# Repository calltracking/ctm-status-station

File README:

= CTM Status Station

The goal this project is to make it easy to have light in a room that helps people in the area know when someone is on a phone call.

We'll subscribe to incoming phone calls and active call events and change the light color to make this obvious

= Setup

Before the device is configured it will expose an access point: 
  ssid: ctmlight
  pass: ctmstatus

After connecting navigate browser to

http://192.168.4.1/

From the web interface configure your networks ssid and password

Once the device joins your network it'll blink green

You'll have to find the device now on your network

http://your-device-ip/

From here you can click connect and you'll be taken to a page on https://app.calltrackingmetrics give access to the device and you should 
next be presented with some options to choose a specific team or your whole account.

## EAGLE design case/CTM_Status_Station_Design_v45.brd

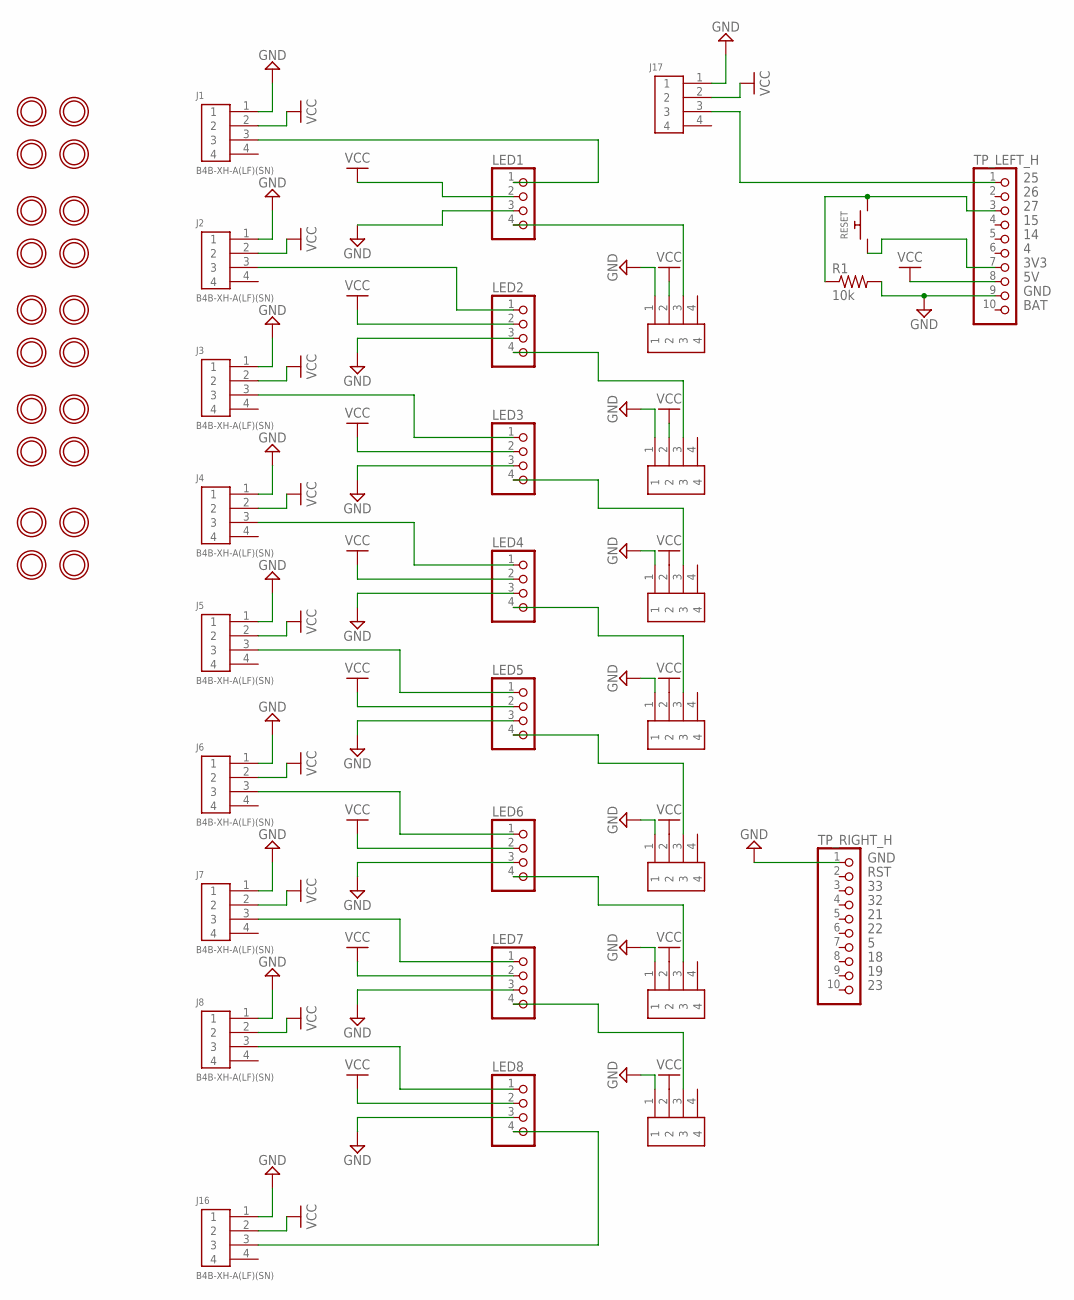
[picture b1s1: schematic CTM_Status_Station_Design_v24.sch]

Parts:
J1, J2, J3, J4, J5, J6, J7, J8, J9, J10, J11, J12, J13, J14, J15, J16, J17: B4B-XH-A(LF)(SN)
LED1, LED2, LED3, LED4, LED5, LED6, LED7, LED8: PINHD-1X4; 1X04
R1: 10k; 0207/7
RESET: SWITCH_PUSHBUTTONEVQ-PE; TACT_PANA-EVQ
TP_LEFT_H: PINHD-1X10; 1X10
TP_RIGHT_H: PINHD-1X10; 1X10
U$1, U$2, U$3, U$4, U$5, U$6, U$7, U$8, U$9, U$10, U$11, U$12, U$13, U$14, U$15, U$16, U$17, U$18, U$19, U$28: MOUNTINGHOLE2.5; MOUNTINGHOLE_2.5_PLATED

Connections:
3V3: RESET.P$1, TP_LEFT_H.7
DIN1: J1.3, LED1.1
DIN2: J2.3, LED2.1
DIN3: J3.3, LED3.1
DIN4: J4.3, LED4.1
DIN5: J5.3, LED5.1
DIN6: J6.3, LED6.1
DIN7: J7.3, LED7.1
DIN8: J8.3, LED8.1
DOUT: J17.3, TP_LEFT_H.1
DOUT1: J10.3, LED1.4
DOUT2: J9.3, LED2.4
DOUT3: J11.3, LED3.4
DOUT4: J12.3, LED4.4
DOUT5: J13.3, LED5.4
DOUT6: J14.3, LED6.4
DOUT7: J15.3, LED7.4
DOUT8: J16.3, LED8.4
GND: J1.1, J2.1, J3.1, J4.1, J5.1, J6.1, J7.1, J8.1, J9.1, J10.1, J11.1, J12.1, J13.1, J14.1, J15.1, J16.1, J17.1, LED1.3, LED2.3, LED3.3, LED4.3, LED5.3, LED6.3, LED7.3, LED8.3, R1.2, TP_LEFT_H.9, TP_RIGHT_H.1
RESET: R1.1, RESET.P$2, TP_LEFT_H.3
VCC: J1.2, J2.2, J3.2, J4.2, J5.2, J6.2, J7.2, J8.2, J9.2, J10.2, J11.2, J12.2, J13.2, J14.2, J15.2, J16.2, J17.2, LED1.2, LED2.2, LED3.2, LED4.2, LED5.2, LED6.2, LED7.2, LED8.2, TP_LEFT_H.8

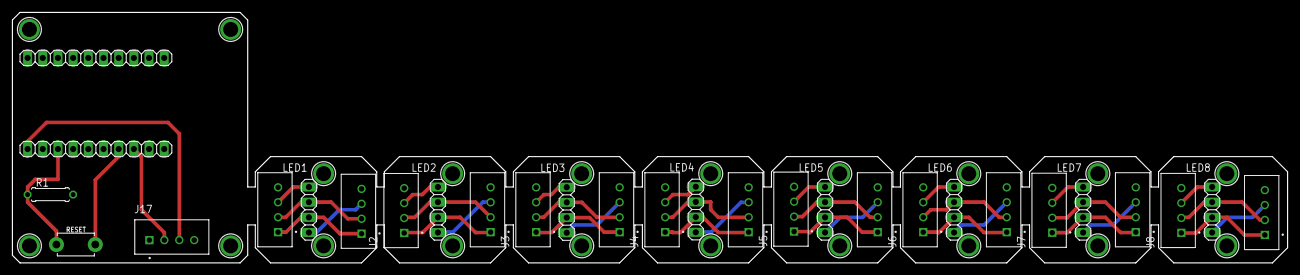
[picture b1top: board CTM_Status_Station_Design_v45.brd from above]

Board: 2 copper layers, 213.4 x 41.9 mm, 49 parts (0 on the bottom side), 21 nets.

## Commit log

2021-10-22 initial work
2021-10-22 formatting
2021-10-22 formating
2021-10-22 format
2021-10-25 more work on login flow
2021-10-30 work on adding a neopixel
2021-11-04 test socketio
2021-11-04 initial work based on active calls counter e.g. global status
2021-11-06 more work on settings
2021-11-07 finished testing with 4 leds... maybe we can try scaling this up 2 8?
2021-11-07 adding logic to handle socket re-connection (maybe don't need two booleans...)
2021-11-07 improve handling of refresh token to get a new access token
2021-11-09 fixing reset and fixed a crash caused by a serial printf
2021-11-11 tweaks and fetch status at boot
2021-11-12 change license
2021-11-12 working on some edge cases related bad memory data on the eeprom
2021-11-12 adding design files
2021-11-12 updating to print with higher temps
2021-11-13 refresh all on save
2021-11-13 update designs to optimize for faster print times and less material per case
2021-11-13 remove pcb peg's they are too small to print quickly
2021-11-13 slightly more optimized layout with 2 parts per print
2021-11-13 fix for ringers we have LED_COUNT ringers
2021-11-14 adding custom status light user defined colors
2021-11-14 sync status using group status call, limited to 10 agents per request but perfect for status station with only 8 led's per node
2021-11-21 refresh all statuses every 60 seconds polling
2021-11-21 make custom statues not as bright
2021-12-02 add 3mf files
2021-12-03 dimmer status lights
2021-12-04 ran into a long running case where the token expired
2021-12-16 usability updates, locate led and possible wifi recovery if lost
    - locate led will change led to yellow/orange for 10 seconds and then refetch status on all leds
    - wifi recovery if the wifi in the office is reset (common as we're getting the new office setup working)
    - we have 8 seats per cube run, this change does reset the device because of eeprom being invalid
2021-12-16 adding some design's for wiring and mounting to exterior cube walls
2021-12-17 fix issues related to led locate
2021-12-23 minor tweaks and notes on development
2022-03-02 update to EIO=4 from 3
2022-03-02 support encoding for lookup of agent name
2022-03-10 cleanup some more output
2022-03-12 work on making it easier to dev
2022-03-13 monitor videos total to ensure we can track on a video
2022-03-14 production toggle need an env way
2022-04-17 recover if account_id is not set
2022-06-08 add feature to support different lights with rgb flipped
2022-07-02 rework for feather board with display
2022-07-02 use the native esp32 HTTPClient
2022-09-29 gotta remember pin out for lights can be 13 or 25 depending on board configuration
2022-10-20 avoid resetting all settings when we just need to reset the wifi
2022-12-02 adding build support for tinys3, pico w not possible due to lack of eeprom
2023-01-23 ran into issue with board not being init and the length of the ssid being too long should* be a good indicator
2023-08-17 work on s3 chip support
2024-02-29 303 before
2024-02-29 let's try this
2024-02-29 adding debug for insight into the url that fails
2024-02-29 avoid dumping the large request
2024-02-29 bounds checking
2024-08-18 Increase custom status break out styles/scripts
    * fix a memory corruption issue if some custom statuses are not used.
2024-08-18 adding button back with a shield need to avoid pulldown
2024-08-18 TODO: make the led count configurable
2025-12-02 captivate for easier setup
2025-12-02 improve error handling
2025-12-02 fix potential buffer overflows
2025-12-02 more memory safety and avoid unnecessary group request
2025-12-02 fix another memory bug
2025-12-03 Adding test coverage and maybe github runner
2025-12-03 need these headers
2025-12-03 platform caching
2025-12-03 adding more tests coverage and refactoring light logic so we can more easily test
2025-12-03 work on modularizing code for improved test coverage
2025-12-03 more tweaks and i think* we need these python files
2025-12-03 ensure we poll for link and redirect
2025-12-03 possible ci coverage fix
2025-12-03 another possible fix
2025-12-03 missed this file for ci
2025-12-03 improve readme
2025-12-03 few nits
2025-12-03 license sweeper
2025-12-03 use local JsonDocument to avoid multi-threaded writes to shared memory that could* lead to corruption
2025-12-04 expanding coverage surface
2025-12-04 increase test coverage
2025-12-04 more testing
2025-12-04 more test improvements
2025-12-04 Fix early disconnect bug
2025-12-05 more coverage
2026-06-03 more work on testing
